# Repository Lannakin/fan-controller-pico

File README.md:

<!-- ./README.md -->
<!-- markdownlint-disable MD013 MD032 MD007 -->
# **Overview** - Fan Controller TXU0204 Pico
<!-- quick summary for github -->
⚠️⚠️⚠️ WARNING ⚠️⚠️⚠️

i am just making this for a hobby.  i have no idea what i am doing.  as you can
see from my profile picture, i am obviously a cat, which means my electrical and
maths skills in general are questionable *at best*.

⚠️⚠️⚠️ WARNING ⚠️⚠️⚠️

i hope github completely mangles my indentation.

using the gratuitously over-qualified raspberry pi pico series, this expansion
board is meant to control up to 4 fan connections **that had better not exceed
1.5a.** they should be 12vdc as well.

pwm output from pico is shifted from 3.3vdc to 5vdc because if i used a 12vdc
noctua fan, that's what noctua expects.  intel recommended supporting 3.3vdc
logic, but that's just a recommendation in what seems to be a de-facto standard,
not an industry requirement.

the current immediate usage scenario is controlling an air filtration box using
a total of 6 [arctic p12 pro pst ln fans](https://www.arctic.de/media/03/4b/1a/1771239441/Spec_Sheet_P12_Pro_PST_LN_EN.pdf).  these fans are daisy-chainable, with
the power and pwm chained to every fan in the series, but (obviously) only the
first fan's tachometer signal connected.

however, i would like this design to support more than 2 channels of fan pwm and
fan tachometer, so that it can be used on other projects.

---

## **CREDITS FOR FONTS**

[WebPlus\_ToshibaSat\_8x14 and WebPlus\_ToshibaSat\_9x16 by VileR](https://**int10h**.org/oldschool-pc-fonts/)

## **Schematic Notes**
<!-- Key circuit blocks, design rationale -->
### expected fan needs gleaned from various documentation

power 12vdc:
12vdc (less than 12.6vdc) power to fan
* current draw per fan probably no higher than 0.7a

power 5vdc:
* rp2040 and rp2350 draw < 0.2A (the datasheets' highest charts were like 37mW
  for the rp2350, and [94.1mA for the pico 2 board from vbus](https://pip-assets.raspberrypi.com/categories/610-raspberry-pi-pico/documents/RP-008307-DS-2-pico-datasheet.pdf#page=13).  these datasheets
  kinda suck)
    * for [cyw43439](https://mm.digikey.com/Volume0/opasdata/d220001/medias/docus/7160/CYW43439KUBGT.pdf), probably around 0.5A
* txu0204 power draw

pwm signal:
* 5vdc pullup, max 5.25vdc
* should be open-collector
* max current 5mA, but device should be capable of 8mA minimum
* 21 - 28kHz is the range for arctic's accepted quality control; 25kHz preferred

tach signal:
* usually pulled up using 12vdc
* noctua says max of 13v, but fan manufacturers probably only expect 5vdc
  can be pulled up to 5vdc or 3.3vdc
* probably open-collector
* max current 5mA, but device should be capable of 8mA minimum
* 2 pulses per revolution

## **Layout Considerations**
<!-- Layer stackup, impedance, keep-outs -->
might be 2 layer
should really be 4 layer sig / gnd / pwr / sig
* oshpark

general routing
* every trace will "try" to return to ground using shortest possible path under?
  the trace
* try to avoid splitting ground planes, and use vias to help keep ground planes
  contiguous
* every time trace uses a via to switch layers, add via to ground as close as
  possible to give the voltage a return shorter path

signal routing:
* if having to cross another signal on another layer, try to do so
  perpendicularly
* try to keep the traces as spread out as possible
* larger traces have better noise rejection

## **Component Notes**
<!-- Click on designators like R1, C5, U3 to highlight on PCB -->
other signal translation component possibilities:
SN74LVC2G17
TXU0204 - integrated pull-down resistors
TXU0202 - integrated pull-down resistors

### TXU0204

"4-Bit Fixed Direction Voltage-Level Translator with Schmitt-Trigger Inputs and
3-State Outputs"

* vcc determines output voltage level
* using 2 to convert pico-output 3v3 pwm signals to 5v fan-input
* using 2 to convert fan-output 5v tachometer signals to 3v3 pico-input
* integrated 5Mohm pull-down resistors

## **Power Distribution**
<!-- Power rails, decoupling strategy -->
syntax of subsections:

```
### (heading size 3) Xvdc rail

device / component on the rail

* note about that device / component
* another note on the device / component
    * subnote on another note
    * another subnote on another note
* yet another note on that device / component
```

### general rail stuff

regarding rail traces / zones in general

* keep rail traces and zones off to the side as much as possible
* attempt to give them clear ground returns with gratuitous vias
* the zones for the positive inputs / outputs are mostly for heat sinking; the
  small size of the traces are plenty for these low voltages and amperages

### 12vdc rail

chanzon [2abn036f](https://www.amazon.com/dp/B07HNV6SBJ) 120vac 1a to 12vdc 3a wall wart:

* claims to be UL listed and shit but i highly doubt it is
* powers pico and this expansion board
* powers 4 x [P12 Pro PST](https://support.arctic.de/p12-pro-pst/docs) @ up to 0.3a each
* powers 1 x [OKI-78SR-5/1.5-W36-C](https://pim.murata.com/asset/pim4/nonIsolatedDCDCconverter/OKI-78SR_PDF_NONISOLATEDDCDCCONVERTER) @ 0.69a
* desired circuit protections: transient, reverse polarity, and overcurrent
  protection; ~~maybe also overvoltage and undervoltage~~ space constraints
    * tvs diode: SMAJ16CA
    * ~~efuse choice 1: [TPS259482A](https://www.ti.com/lit/gpn/TPS25948)~~ space constraints
        * protects against overvoltage, overcurrent, shorts, reverse current,
          undervoltage
    * ~~efuse choice 2: [TPS259472A](https://www.ti.com/lit/ds/symlink/tps25947.pdf)~~ space constraints
        * protects against overvoltage, overcurrent, shorts, reverse current,
          reverse polarity, undervoltage
    * reverse polarity protection
        * p-mosfet
    * input tvs diodes on main power and +12vdc fan pins
        * bidirectional to protect against surges from GND
    * current limit
    * input limit <=2A 12vdc to 5vdc psu
    * idk for fans
* may need filtering but i don't own a real oscilloscope soooooooooo

OKI-78SR-5/1.5-W36-C (12vdc input):

* based on [MP2467](https://www.monolithicpower.com/en/documentview/productdocument/index/version/2/document_type/Datasheet/lang/en/sku/MP2467/document_id/263/)
* recommends 2a fuse
* **inrush transient**: 0.16 A2-Sec.
* might need an electrolytic capacitor for up to 3ft of "20awg" wire from the
  wall wart to prevent instability or whatever
* no mention of needing input filtering;  that's very bold of you, murata
* the only filtering mentioned appears to be what is physically on the module's
  pcb: 2x 100uF (ceramic capacitors)
* desired circuit protections: counter-emf schottky diode
    * schottky diode SGL1-20 for protection against counter-emf when power is
      shut off if fuse blows / power is lost
    * output of 12vdc to 5vdc psu has built-in limiter
* with supposed ripple of 30mV peak-to-peak, doubt additional filtering is
  neeeded

### 5vdc rail

OKI-78SR-5/1.5-W36-C (5vdc output):

* output of 5vdc at up to 1.5a
* mostly selected because it's in my drawer from years ago and has like <30mV
  ripple, which appears to be completely obscene even at like $6
* the okami series that this dcdc module is from has a cool wolf logo
* no mention of adding additional filtering; output filtering on the module pcb
  (assuming that's what "Cvbus" is) is 1x 1000uF (ceramic capacitor)

pico supplying via vsys

* raspberry pi pico datasheets [rec using p-mosfet DMG2305UX or a schottky diode](https://pip-assets.raspberrypi.com/categories/610-raspberry-pi-pico/documents/RP-008307-DS-2-pico-datasheet.pdf#page=21)
    * ORing circuit for 5vdc vbus < - > vsys
        * diode - feel like Vf drop too high, might hinder fans' pwm input
        * p-mosfet - i ain't wanna do another one of these
        * ORing dual ideal diode
        * lm66200 is like \$0.60 each max, cool, simple, and small, vs p-fet at
          like \$0.45 each, 40 mΩ on-resistance

### 3.3vdc rail

pico 5vdc to 3.3vdc converter (same for pico, w, 2, 2w): [RT6150](https://www.richtek.com/assets/product_file/RT6150A=RT6150B/DS6150AB-06.pdf)

* note that the datasheet won't fully cover the converter's output capabilities
  b/c the converter is the sum of the conversion circuit
* [super noisy in power save mode](https://pico-adc.markomo.me/PSU-Noise/) (115mV pk-pk vs 31mV); power efficiency is
  much worse, though
* maybe should use linear regulator
* if using analog, rec use external shunt ref like [lm4040](https://www.ti.com/lit/ds/symlink/lm4040.pdf) (in case using
  potentiometer for fan speed setting)
    * note: someone said for a human-operated potentiometer, the precision
      probably doesn't matter
* recommended: stay under 300mA

## **Signal Integrity**
<!-- Critical nets, routing constraints -->
this should probably be a 4-layer board, i don't think i can avoid splitting the
ground plane.

## **References**
<!-- Datasheets, application notes, calculations -->
### pcb production

oshpark:
  [oshpark - 2 layer prototype service](https://docs.oshpark.com/services/two-layer/)
  [oshpark - after dark (also 2 layer) service](https://docs.oshpark.com/services/afterdark/)
  [oshpark - 4 layer prototype service](https://docs.oshpark.com/services/four-layer/)

digikey:
  [pcb builder - faq](https://www.digikey.com/en/resources/design-tools/pcb-faqs)
  [pcb builder - technical specs](https://www.digikey.com/en/resources/design-tools/pcb-builder-technical-specs)

### efuses

[texas instruments "basics of efuses"](https://www.ti.com/lit/an/slva862a/slva862a.pdf)

### general 12vdc pwm fan control (pc fans)

[intel corporation "4-wire pulse width modulation (pwm) controlled fans"](https://glkinst.com/cables/cable_pics/4_Wire_PWM_Spec.pdf)
  reference to pulling up to 12v power to fans on tachometer pin

[edn article "4 wire pc fan"](https://www.edn.com/4-wire-pc-fan/)
[yoinked motherboard schematic picture from edn article](https://www.edn.com/wp-content/uploads/2019/12/2-Fan-Connector-Scheme.png)
  pulls up to 12v power to fans on tachometer pin

[texas instruments "fan controller overview"](https://www.ti.com/lit/po/sprt839/sprt839.pdf)
  "The tachometer output from the fan is
  typically an open-collector (or open-drain) output that requires a pull-up
  resistor. It's customary to connect this pull-up to the same voltage as the fan
  power."
  "you can still pull up to a lower voltage though" (slight paraphrasing)

### arctic p12 pro pst (ln)

[pwm curve for p12 pro pst series](https://support.arctic.de/products/p12-pro-pst/techdocs/P12%20Pro%20Series_PWMcurve.pdf)
[p12 pro pst docs page](https://support.arctic.de/p12-pro-pst/docs)
[p12 pro pst pwm guidelines](https://support.arctic.de/p12-pro-pst#toc-103)
[p12 pro pst ln docs page](https://support.arctic.de/p12-pro-pst-ln/docs)
[p12 pst pro ln pwm guidelines](https://support.arctic.de/p12-pro-pst-ln#toc-107)

### noctua fan jumpscare

[noctua "noctua pwm specifications white paper"](https://cdn.noctua.at/preview/media/Noctua_PWM_specifications_white_paper.pdf) Vtachometer for 12V fans: 5V
  recommended (13V max.)" at <5mA for 12v fans

### raspberry pi pico boards

[pico power supply](https://pip-assets.raspberrypi.com/categories/610-raspberry-pi-pico/documents/RP-008307-DS-2-pico-datasheet.pdf#page=21)
  note: this applies to pico, pico w, pico 2, pico 2w

---

### layout filched from [KiNotes](https://pcbtools.xyz/tools/kinotes)

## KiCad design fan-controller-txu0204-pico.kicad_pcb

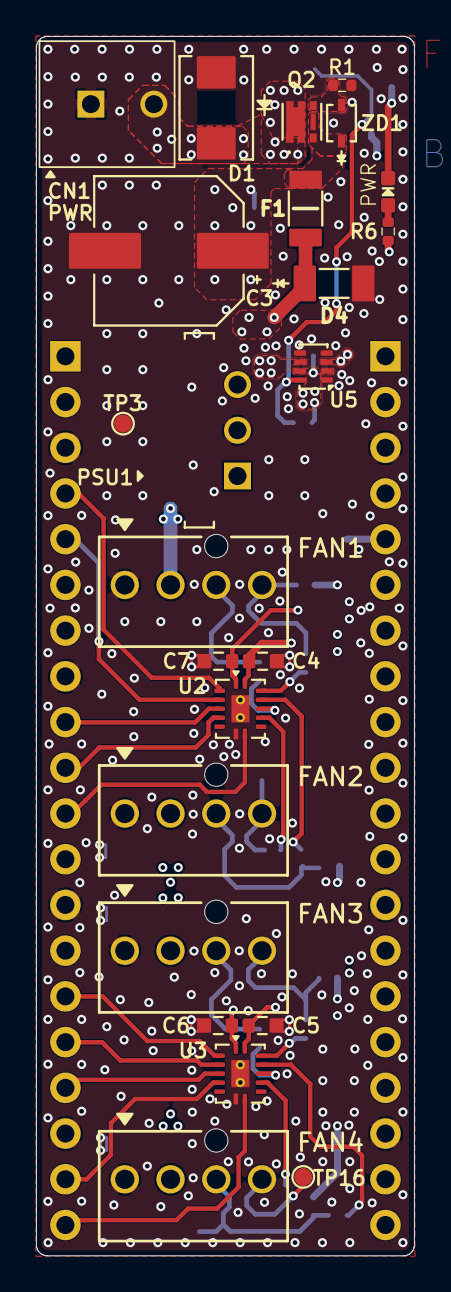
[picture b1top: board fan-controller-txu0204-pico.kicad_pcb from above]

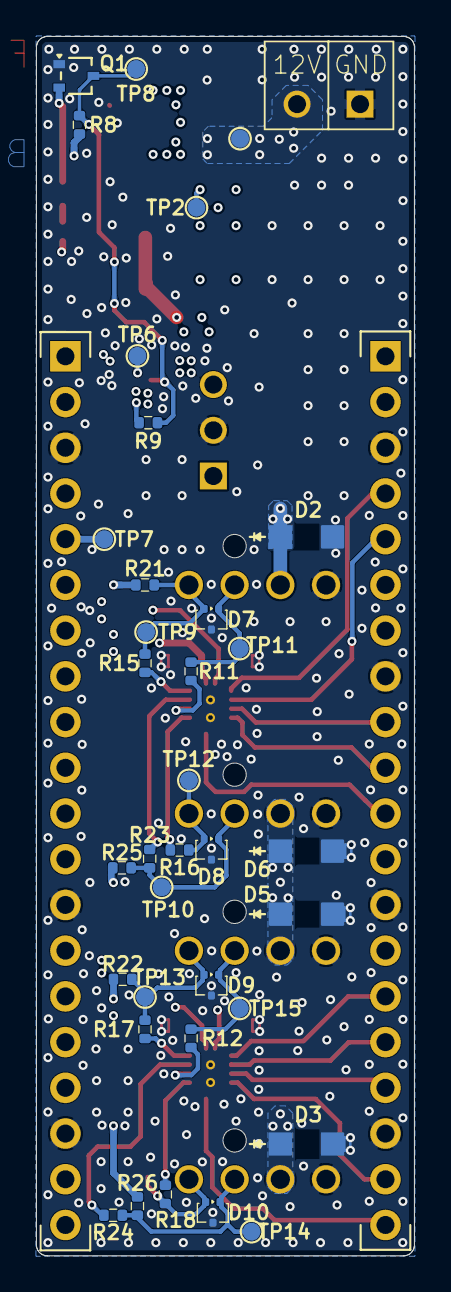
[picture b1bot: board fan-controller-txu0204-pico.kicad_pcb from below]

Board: 4 copper layers, 21.0 x 67.7 mm, 61 parts (37 on the bottom side), 38 nets.

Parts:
C3: 220uF; CAP_EEE-FT-SIZE-CODE-F_8x10_PANASONIC
C4, C5, C6, C7: 1uF; C_GRM18_0603_1608Metric_MURATA
CN1: PWR; 2-POS_FK-MPT_1891069_PHOENIX
CN2: RaspberryPi_Pico; RPI_Pico-CN_Left
CN3: RaspberryPi_Pico; RPI_Pico-CN_Right
D1: SMAJ16CA; DIO_SMB_LOWVOLTAGE_DIODES
D2, D3, D5, D6: SMF12A; D_SOD-123F_EATON
D4: SGL1-20; DIO_DO213AA_MINIMELF
D7, D8, D9, D10: DF3A5.6FV; TRANS_SOT-723
F1: 2016L150/33DR; PTS1206_FUSC3216X68N_EATON
FAN1, FAN2, FAN3, FAN4: Conn_01x04; 470531000_4-POS-MALE-HEADER-VERTICAL_FAN_MOLEX
LD1: VSYS; LED_599-00XX-137F_0603_1608Metric
PSU1: OKI-78SR-5/1.5-W36-C; CONV_OKI-78SR-W36-C_MURATA2
Q1: RU1C002ZP; SOT-323T-3_SOT-323FL_SC-85
Q2: DMP3014SFDE; TRANS_6-UDFN_U-DFN2020-6-E_DIO
R1: 274; R_RK37H_0402_1005Metric_KOA
R6: 180; R_RK37H_0402_1005Metric_KOA
R8: 47k; R_RK37H_0402_1005Metric_KOA
R9: 5.62k; R_RK37H_0402_1005Metric_KOA
R11, R12, R15, R16, R17, R18, R21, R22, R23, R24, R25, R26: 750; R_RK37H_0402_1005Metric_KOA
TP1: 12VIN; TestPoint_Pad_D1.0mm
TP2: 12PROT; TestPoint_Pad_D1.0mm
TP3: GND; TestPoint_Pad_D1.0mm
TP6: VSYS; TestPoint_Pad_D1.0mm
TP7: 3V3; TestPoint_Pad_D1.0mm
TP8: SGD; TestPoint_Pad_D1.0mm
TP9: PWF1; TestPoint_Pad_D1.0mm
TP10: PWF2; TestPoint_Pad_D1.0mm
TP11: TCF1; TestPoint_Pad_D1.0mm
TP12: TCF2; TestPoint_Pad_D1.0mm
TP13: PWF3; TestPoint_Pad_D1.0mm
TP14: PWF4; TestPoint_Pad_D1.0mm
TP15: TCF3; TestPoint_Pad_D1.0mm
TP16: TCF4; TestPoint_Pad_D1.0mm
U2, U3: TXU0204; DHWQFN-14-1EP_2.5x3mm_P0.5mm_EP1x1.5mm_ThermalVias
U5: LM66200; SOT-583_SOT-5X3_DRL0008A_TEX
ZD1: MM3Z20B-AQ; D_SOD-323F_SOD323F_DIODES

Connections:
+3.3VDC: C6.1, C7.1, CN3.36 (3V3), TP7.1 (1_1), U2.1 (VCCA), U3.1 (VCCA)
+5VDC: C4.1, C5.1, CN3.39 (VSYS), R6.2, R8.2, R9.2, R21.2, R22.2, R25.2, R26.2, TP6.1 (1_1), U2.14 (VCCB), U3.14 (VCCB), U5.2 (VOUT), U5.7 (VOUT)
+12VDC: C3.1, D2.1 (K), D3.1 (K), D5.1 (K), D6.1 (K), F1.1, FAN1.2, FAN2.2, FAN3.2, FAN4.2, Q2.3 (SOURCE), Q2.4 (SOURCE), TP2.1 (1_1), ZD1.1 (K)
/5V_PSU1_OUT: PSU1.3 (OUT), U5.6 (VIN2)
/+12V_FUSED_PSU1: D4.1 (K), F1.2, PSU1.1 (IN)
/+12V_UNPROTECTED: CN1.2 (+12VDC), D1.1 (A1), Q2.1 (DRAIN), TP1.1 (1_1)
/ENABLE_FAN1FAN2: CN2.11 (GPIO8), U2.8 (OE)
/ENABLE_FAN3FAN4: CN2.20 (GPIO15), U3.8 (OE)
/LM66200_STAT: Q1.3 (GATE), R8.1, R9.1, TP8.1 (1_1), U5.8 (ST)
/PICO_PWM_FAN1: CN2.4 (GPIO2), U2.2 (A1)
/PICO_PWM_FAN2: CN2.5 (GPIO3), U2.3 (A2)
/PICO_PWM_FAN3: CN2.15 (GPIO11), U3.2 (A1)
/PICO_PWM_FAN4: CN2.16 (GPIO12), U3.3 (A2)
/PICO_TACH_FAN1: CN2.9 (GPIO6), U2.4 (A3Y)
/PICO_TACH_FAN2: CN2.10 (GPIO7), U2.5 (A4Y)
/PICO_TACH_FAN3: CN2.17 (GPIO13), U3.4 (A3Y)
/PICO_TACH_FAN4: CN2.19 (GPIO14), U3.5 (A4Y)
/PWM_FAN1: R15.2, U2.13 (B1Y)
/PWM_FAN2: R23.2, U2.12 (B2Y)
/PWM_FAN3: R17.2, U3.13 (B1Y)
/PWM_FAN4: R24.2, U3.12 (B2Y)
/TACH_FAN1: R11.2, U2.11 (B3)
/TACH_FAN2: R16.2, U2.10 (B4)
/TACH_FAN3: R12.2, U3.11 (B3)
/TACH_FAN4: R18.2, U3.10 (B4)
/V_{GS}_LIM: Q2.2 (GATE), R1.2, ZD1.2
GND: C3.2, C4.2, C5.2, C6.2, C7.2, CN1.1 (GND), CN2.3 (GND), CN2.8 (GND), CN2.13 (GND), CN2.18 (GND), CN3.23 (GND), CN3.28 (GND), CN3.38 (GND), D1.2 (A2), D2.2 (A), D3.2 (A), D4.2 (A), D5.2 (A), D6.2 (A), D7.3 (A), D8.3 (A), D9.3 (A), D10.3 (A), FAN1.1, FAN2.1, FAN3.1, FAN4.1, PSU1.2 (GND), Q1.1 (SOURCE), R1.1, TP3.1 (1_1), U2.7 (GND), U2.15 (PAD), U3.7 (GND), U3.15 (PAD), U5.1 (GND), U5.4 (~ON), U5.5 (GND)
unnamed: D7.1 (K1), FAN1.3, R11.1, TP11.1 (1_1)
unnamed: D7.2 (K2), FAN1.4, R15.1, R21.1, TP9.1 (1_1)
unnamed: D8.1 (K1), FAN2.3, R23.1, R25.1, TP10.1 (1_1)
unnamed: D8.2 (K2), FAN2.4, R16.1, TP12.1 (1_1)
unnamed: D9.1 (K1), FAN3.3, R12.1, TP15.1 (1_1)
unnamed: D9.2 (K2), FAN3.4, R17.1, R22.1, TP13.1 (1_1)
unnamed: D10.1 (K1), FAN4.3, R24.1, R26.1, TP14.1 (1_1)
unnamed: D10.2 (K2), FAN4.4, R18.1, TP16.1 (1_1)
unnamed: LD1.2 (A), R6.1
unnamed: LD1.1 (K), Q1.2 (DRAIN)
VBUS: CN3.40 (VBUS), U5.3 (VIN1)
